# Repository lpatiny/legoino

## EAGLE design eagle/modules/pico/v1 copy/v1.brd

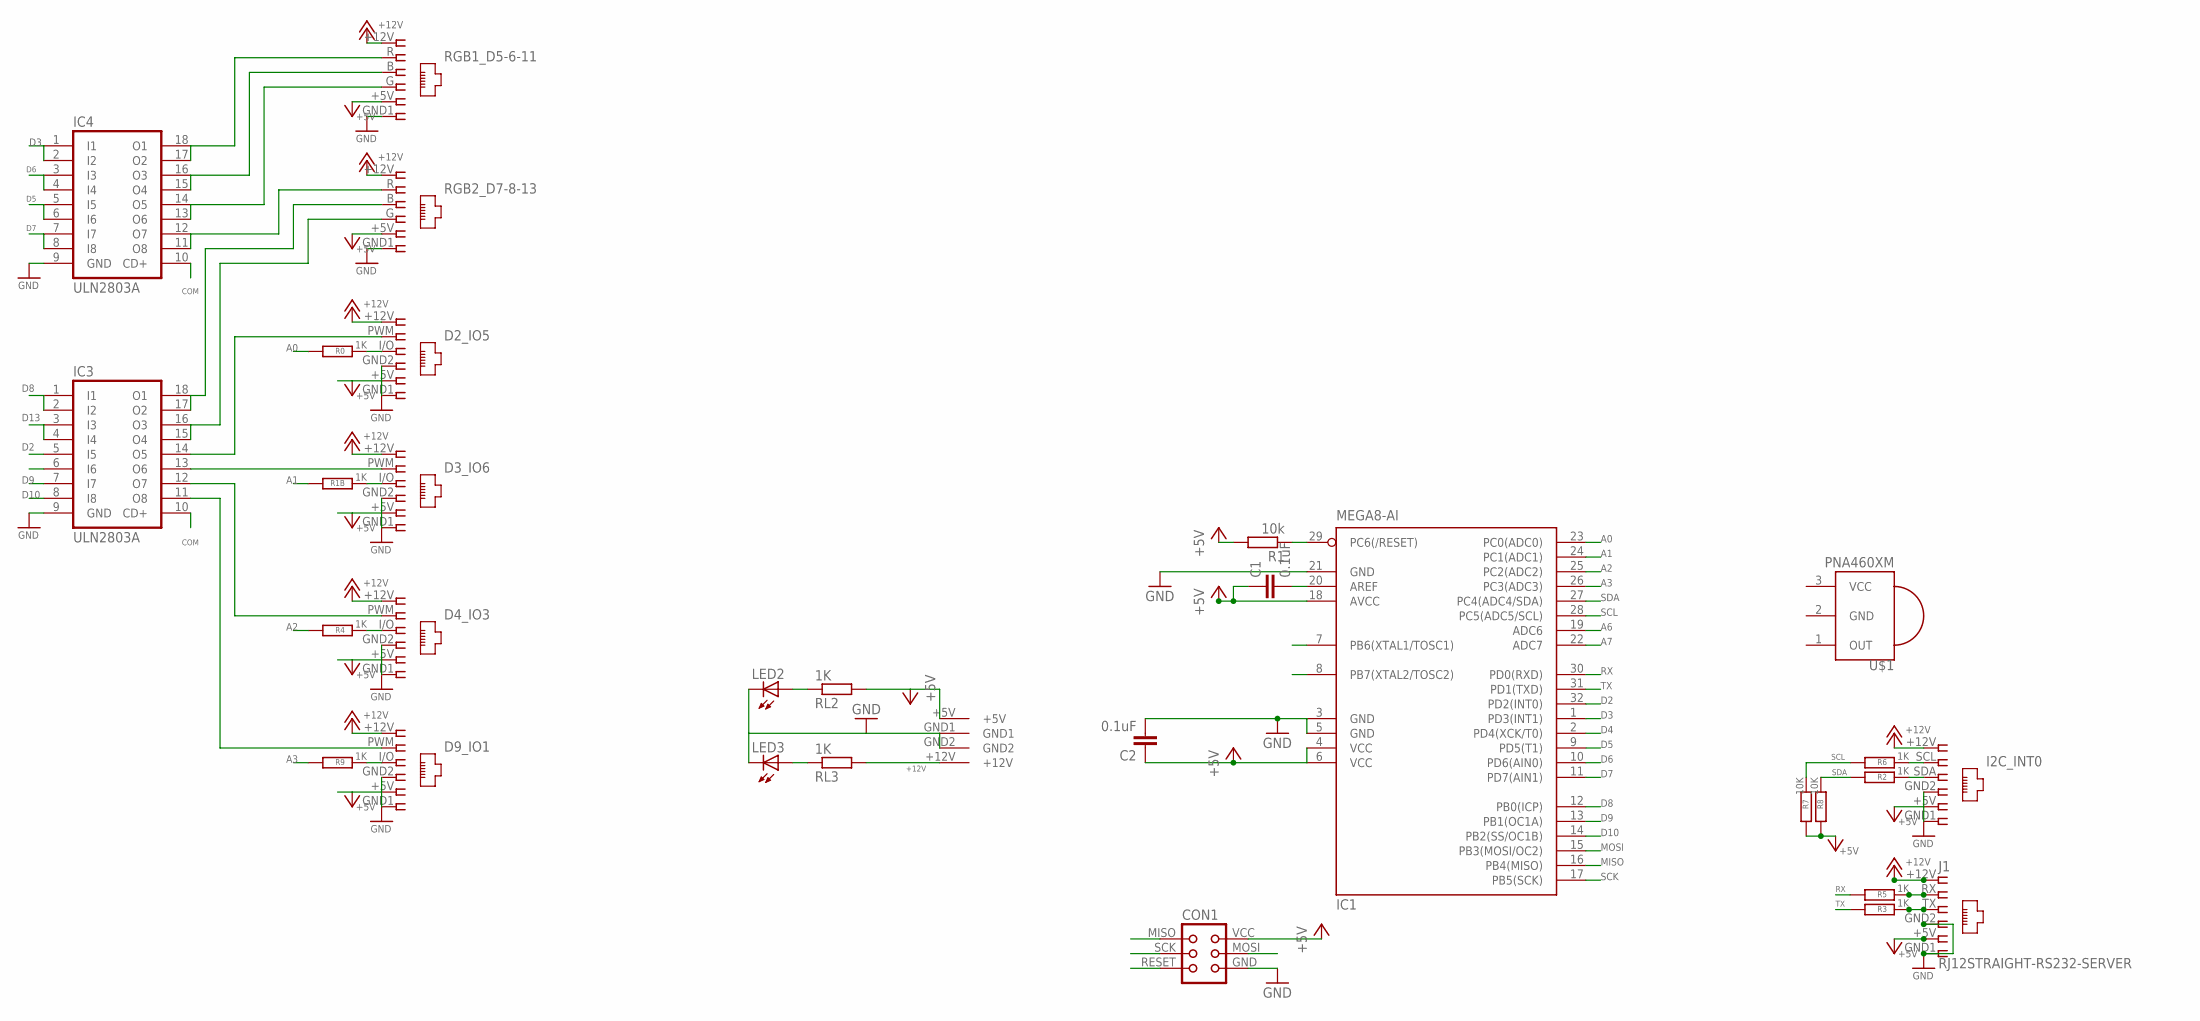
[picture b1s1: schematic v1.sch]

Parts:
C1, C2: 0.1uF; C1206
CON1: TINYISP
D2_IO5: IO5; RJ12-STRAIGHT
D3_IO6: IO6; RJ12-STRAIGHT
D4_IO3: IO3; RJ12-STRAIGHT
D9_IO1: IO1; RJ12-STRAIGHT
I2C_INT0: I2C; RJ12-STRAIGHT-I2C
IC1: MEGA8-AI; TQFP32-08
IC3, IC4: ULN2803A; SO18W
J1: RJ12STRAIGHT-RS232-SERVER; RJ12-STRAIGHT-RS232
LED2, LED3: LED3MM
R0, R1B, R2, R3, R4, R5, R6, R9: 1K; M1206
R1: 10k; M1206
R7, R8: 10K; M1206
RGB1_D5-6-11: RGB1; RJ12-STRAIGHT-RGB
RGB2_D7-8-13: RGB2; RJ12-STRAIGHT-RGB
RL2, RL3: 1K; M1206
U$1: PNA460XM
U$2: KPJX-4S-S

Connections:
+5V: C1.1, C2.1, CON1.VCC, D2_IO5.+5V (5), D3_IO6.+5V (5), D4_IO3.+5V (5), D9_IO1.+5V (5), I2C_INT0.+5V (5), IC1.4 (VCC), IC1.6 (VCC), IC1.18 (AVCC), J1.+5V (5), R1.2, R7.2, R8.2, RGB1_D5-6-11.+5V (5), RGB2_D7-8-13.+5V (5), RL2.2, U$2.+5V
+12V: D2_IO5.+12V (1), D3_IO6.+12V (1), D4_IO3.+12V (1), D9_IO1.+12V (1), I2C_INT0.+12V (1), J1.+12V (1), RGB1_D5-6-11.+12V (1), RGB2_D7-8-13.+12V (1), RL3.2, U$2.+12V
A0: IC1.23 (PC0(ADC0)), R0.2
A1: IC1.24 (PC1(ADC1)), R1B.2
A2: IC1.25 (PC2(ADC2)), R4.2
A3: IC1.26 (PC3(ADC3)), R9.2
A6: IC1.19 (ADC6)
A7: IC1.22 (ADC7)
COM: IC3.10 (CD+), IC4.10 (CD+)
D2: IC1.32 (PD2(INT0)), IC3.5 (I5)
D2B: D4_IO3.I/O (3), R4.1
D2B1: D9_IO1.I/O (3), R9.1
D2B4: I2C_INT0.SDA (3), R2.1
D2B5: J1.TX (3), R3.1
D2B6: D2_IO5.I/O (3), R0.1
D2B7: D3_IO6.I/O (3), R1B.1
D3: IC1.1 (PD3(INT1)), IC4.1 (I1), IC4.2 (I2)
D4: IC1.2 (PD4(XCK/T0))
D5: IC1.9 (PD5(T1)), IC4.5 (I5), IC4.6 (I6)
D6: IC1.10 (PD6(AIN0)), IC4.3 (I3), IC4.4 (I4)
D7: IC1.11 (PD7(AIN1)), IC4.7 (I7), IC4.8 (I8)
D8: IC1.12 (PB0(ICP)), IC3.1 (I1), IC3.2 (I2)
D9: IC1.13 (PB1(OC1A)), IC3.7 (I7)
D10: IC1.14 (PB2(SS/OC1B)), IC3.8 (I8)
D13: IC3.3 (I3), IC3.4 (I4)
GND: C2.2, CON1.GND, D2_IO5.GND1 (6), D2_IO5.GND2 (4), D3_IO6.GND1 (6), D3_IO6.GND2 (4), D4_IO3.GND1 (6), D4_IO3.GND2 (4), D9_IO1.GND1 (6), D9_IO1.GND2 (4), I2C_INT0.GND1 (6), I2C_INT0.GND2 (4), IC1.3 (GND), IC1.5 (GND), IC1.21 (GND), IC3.9 (GND), IC4.9 (GND), J1.GND1 (6), J1.GND2 (4), LED2.K (C), LED3.K (C), RGB1_D5-6-11.GND1 (6), RGB2_D7-8-13.GND1 (6), U$1.2 (GND), U$2.GND1, U$2.GND2
MISO: CON1.MISO, IC1.16 (PB4(MISO))
MOSI: CON1.MOSI, IC1.15 (PB3(MOSI/OC2))
unnamed: D3_IO6.PWM (2), IC3.13 (O6)
unnamed: C1.2, IC1.20 (AREF)
unnamed: D4_IO3.PWM (2), IC3.12 (O7)
unnamed: IC3.17 (O2), IC3.18 (O1), RGB2_D7-8-13.B (3)
unnamed: IC4.17 (O2), IC4.18 (O1), RGB1_D5-6-11.R (2)
unnamed: IC4.15 (O4), IC4.16 (O3), RGB1_D5-6-11.B (3)
unnamed: D9_IO1.PWM (2), IC3.11 (O8)
unnamed: IC3.15 (O4), IC3.16 (O3), RGB2_D7-8-13.G (4)
unnamed: D2_IO5.PWM (2), IC3.14 (O5)
unnamed: IC4.13 (O6), IC4.14 (O5), RGB1_D5-6-11.G (4)
unnamed: IC4.11 (O8), IC4.12 (O7), RGB2_D7-8-13.R (2)
unnamed: J1.RX (2), R5.1
unnamed: I2C_INT0.SCL (2), R6.1
unnamed: LED3.A, RL3.1
unnamed: LED2.A, RL2.1
RESET: CON1.RESET, IC1.29 (PC6(/RESET)), R1.1
RX: IC1.30 (PD0(RXD)), R5.2
SCK: CON1.SCK, IC1.17 (PB5(SCK))
SCL: IC1.28 (PC5(ADC5/SCL)), R6.2, R7.1
SDA: IC1.27 (PC4(ADC4/SDA)), R2.2, R8.1
TX: IC1.31 (PD1(TXD)), R3.2
VCC: U$1.3 (VCC)

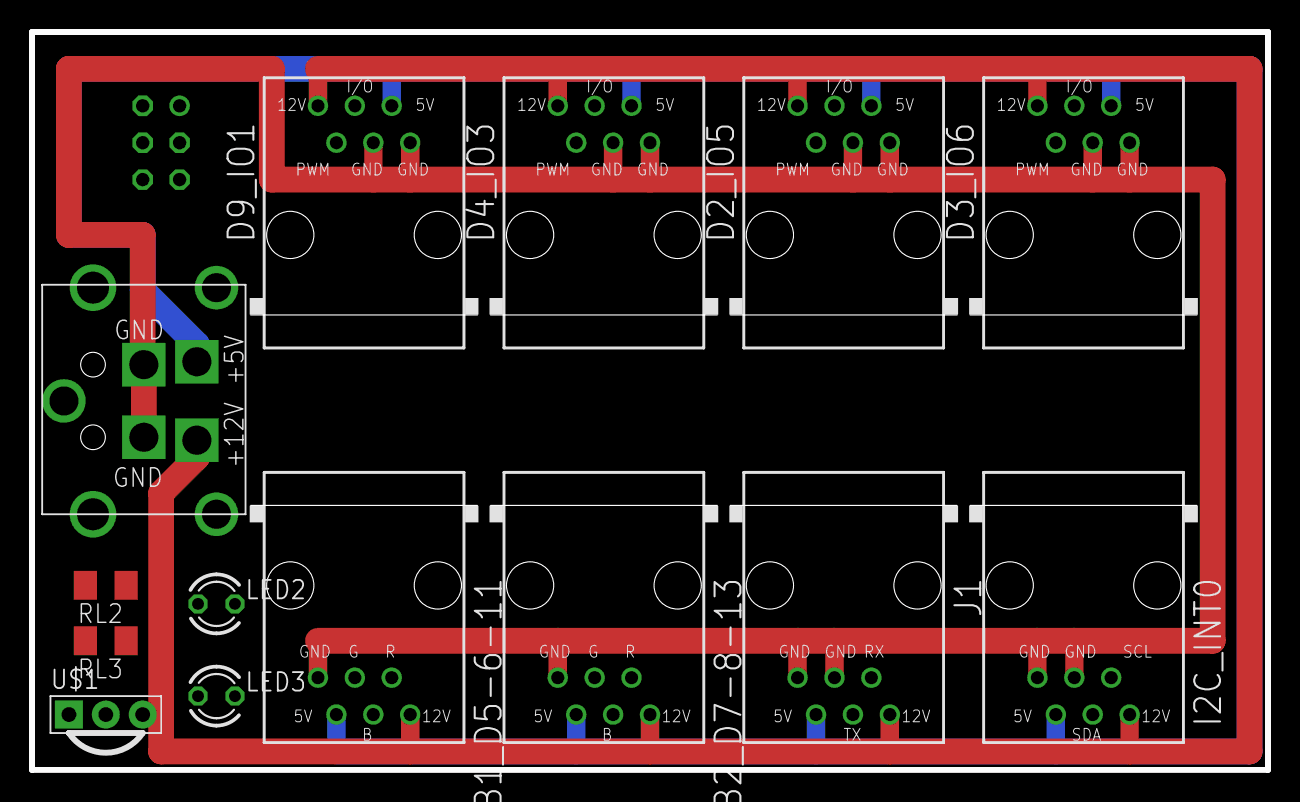
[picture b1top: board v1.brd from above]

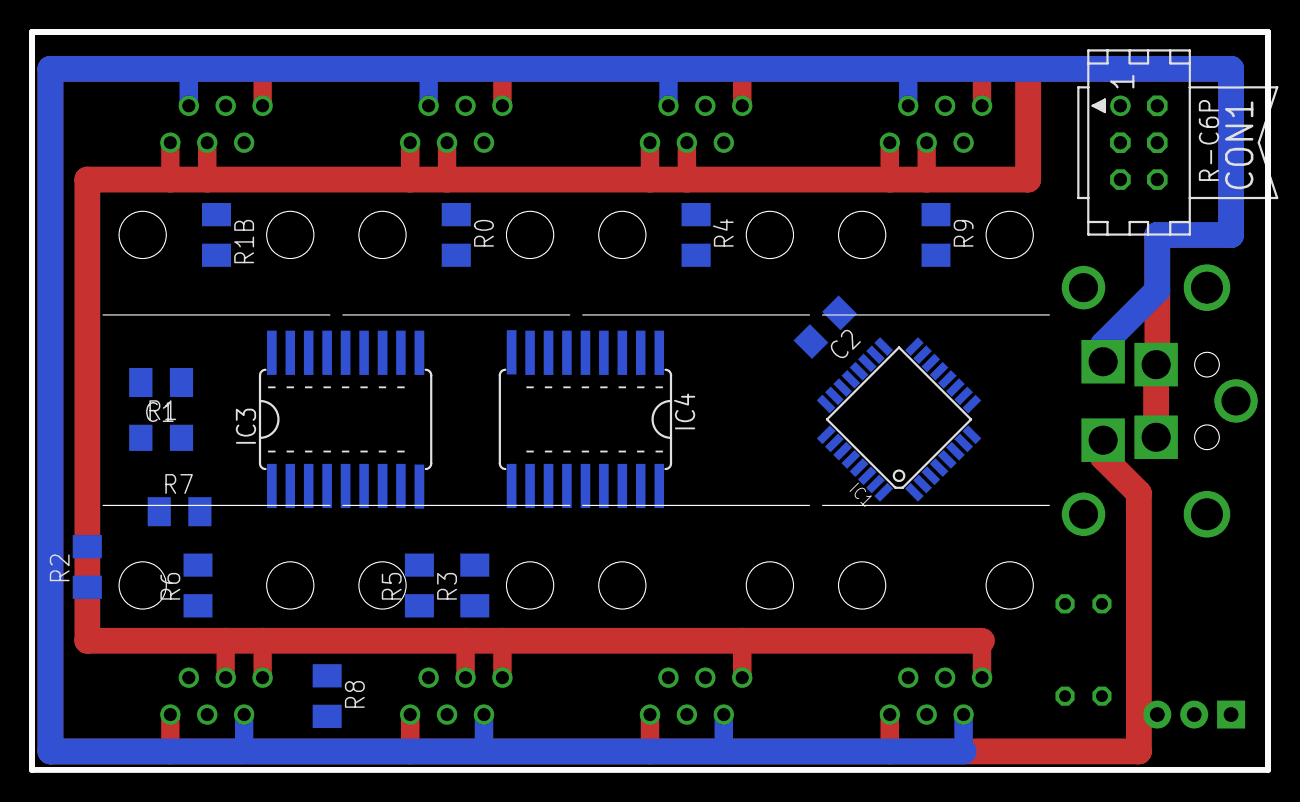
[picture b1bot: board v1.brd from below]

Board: 2 copper layers, 85.1 x 50.8 mm, 31 parts (17 on the bottom side), 46 nets.

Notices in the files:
parts and their libraries:
tag-connect: ©2009 ROFA.cz - modified and updated by Robert Darlington ‹rdarlington@gmail.com›
SparkFun: Licensing: CC v3.0 Share-Alike You are welcome to use this library for commercial purposes.
